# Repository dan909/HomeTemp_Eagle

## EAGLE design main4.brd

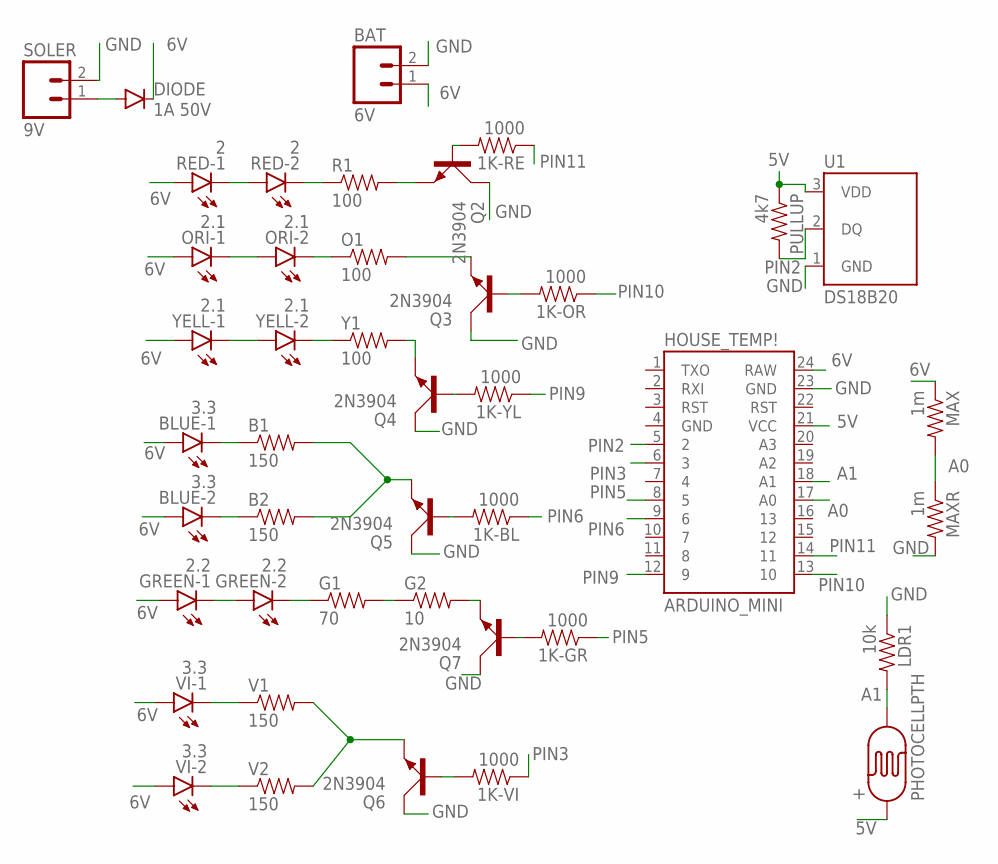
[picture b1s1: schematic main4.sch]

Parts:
1K-BL, 1K-GR, 1K-OR, 1K-RE, 1K-VI, 1K-YL: 1000; AXIAL-0.3
+: PHOTOCELLPTH; PHOTOCELL
B1, B2: 150; AXIAL-0.3
BAT: 6V; 1X02
BLUE-1, BLUE-2: 3.3; LED10MM
DIODE: 1A 50V; DIODE-1N4001
G1: 70; AXIAL-0.3
G2: 10; AXIAL-0.3
GREEN-1, GREEN-2: 2.2; LED10MM
HOUSE_TEMP!: ARDUINO_MINI
LDR1: 10k; AXIAL-0.3
MAX: 1m; AXIAL-0.3
MAXR: 1m; AXIAL-0.3
O1: 100; AXIAL-0.3
ORI-1, ORI-2: 2.1; LED10MM
PULLUP: 4k7; AXIAL-0.3
Q2, Q3, Q4, Q5, Q6, Q7: 2N3904; TO92D
R1: 100; AXIAL-0.3
RED-1, RED-2: 2; LED10MM
SOLER: 9V; 1X02
U1: DS18B20; TO-92-AMMO
V1, V2: 150; AXIAL-0.3
VI-1, VI-2: 3.3; LED10MM
Y1: 100; AXIAL-0.3
YELL-1, YELL-2: 2.1; LED10MM

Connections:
5V: +.1, HOUSE_TEMP!.21 (VCC), PULLUP.P$1 (1), U1.3 (VDD)
6V: BAT.1, BLUE-1.A, BLUE-2.A, DIODE.C, GREEN-1.A, HOUSE_TEMP!.24 (RAW), MAX.P$1 (1), ORI-1.A, RED-1.A, VI-1.A, VI-2.A, YELL-1.A
A0: HOUSE_TEMP!.17 (A0), MAX.P$2 (2), MAXR.P$1 (1)
A1: +.2, HOUSE_TEMP!.18 (A1), LDR1.P$2 (2)
BLU: B1.P$1 (1), BLUE-1.C
BLU2: B2.P$1 (1), BLUE-2.C
GND: BAT.2, HOUSE_TEMP!.23 (GND), LDR1.P$1 (1), MAXR.P$2 (2), Q2.C, Q3.C, Q4.C, Q5.C, Q6.C, Q7.C, SOLER.2, U1.1 (GND)
GREEN-2: G1.P$1 (1), GREEN-2.C
GREN: GREEN-1.C, GREEN-2.A
unnamed: R1.P$1 (1), RED-2.C
unnamed: DIODE.A, SOLER.1
unnamed: Y1.P$1 (1), YELL-2.C
unnamed: Q4.E, Y1.P$2 (2)
unnamed: B1.P$2 (2), B2.P$2 (2), Q5.E
unnamed: Q6.E, V1.P$2 (2), V2.P$2 (2)
unnamed: Q2.E, R1.P$2 (2)
unnamed: O1.P$2 (2), Q3.E
unnamed: G1.P$2 (2), G2.P$1 (1)
unnamed: G2.P$2 (2), Q7.E
unnamed: 1K-VI.P$2 (2), Q6.B
unnamed: 1K-GR.P$2 (2), Q7.B
unnamed: 1K-BL.P$2 (2), Q5.B
unnamed: 1K-YL.P$2 (2), Q4.B
unnamed: 1K-OR.P$2 (2), Q3.B
unnamed: 1K-RE.P$2 (2), Q2.B
O1: O1.P$1 (1), ORI-2.C
ORI: ORI-1.C, ORI-2.A
PIN2: HOUSE_TEMP!.5 (2), PULLUP.P$2 (2), U1.2 (DQ)
PIN3: 1K-VI.P$1 (1), HOUSE_TEMP!.6 (3)
PIN5: 1K-GR.P$1 (1), HOUSE_TEMP!.8 (5)
PIN6: 1K-BL.P$1 (1), HOUSE_TEMP!.9 (6)
PIN9: 1K-YL.P$1 (1), HOUSE_TEMP!.12 (9)
PIN10: 1K-OR.P$1 (1), HOUSE_TEMP!.13 (10)
PIN11: 1K-RE.P$1 (1), HOUSE_TEMP!.14 (11)
RED: RED-1.C, RED-2.A
VI: V1.P$1 (1), VI-1.C
VI2: V2.P$1 (1), VI-2.C
YEL: YELL-1.C, YELL-2.A

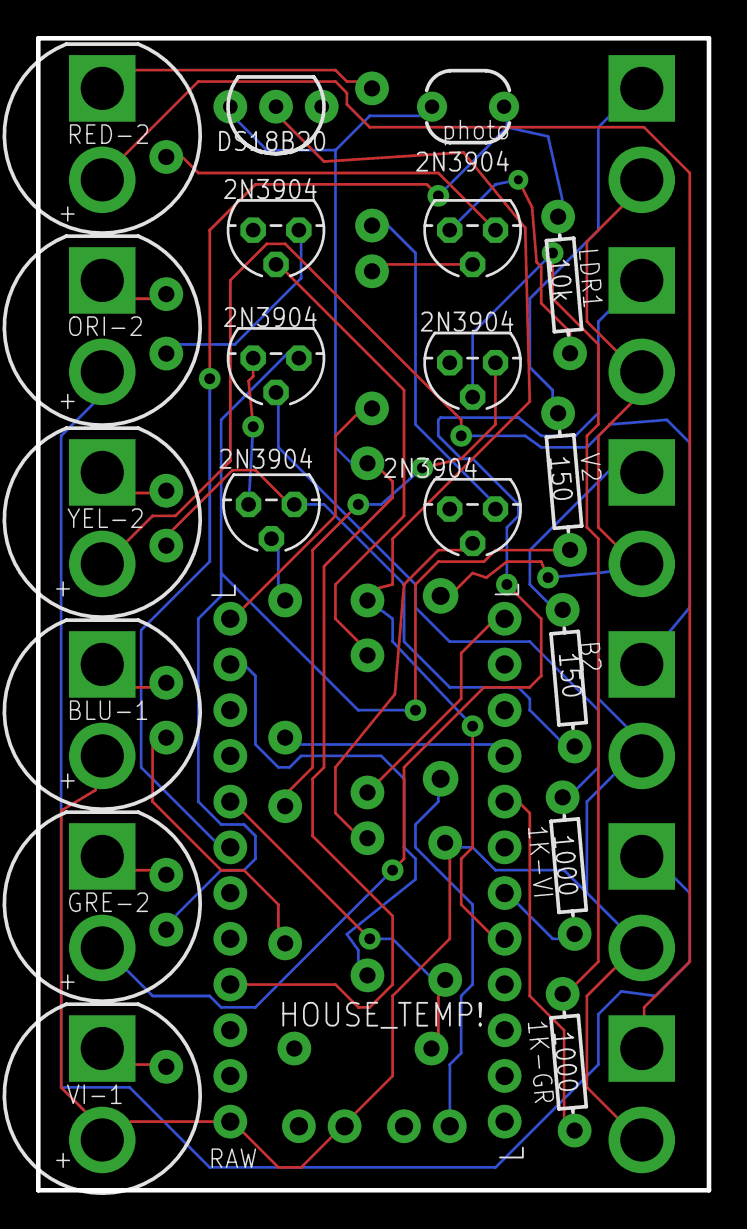
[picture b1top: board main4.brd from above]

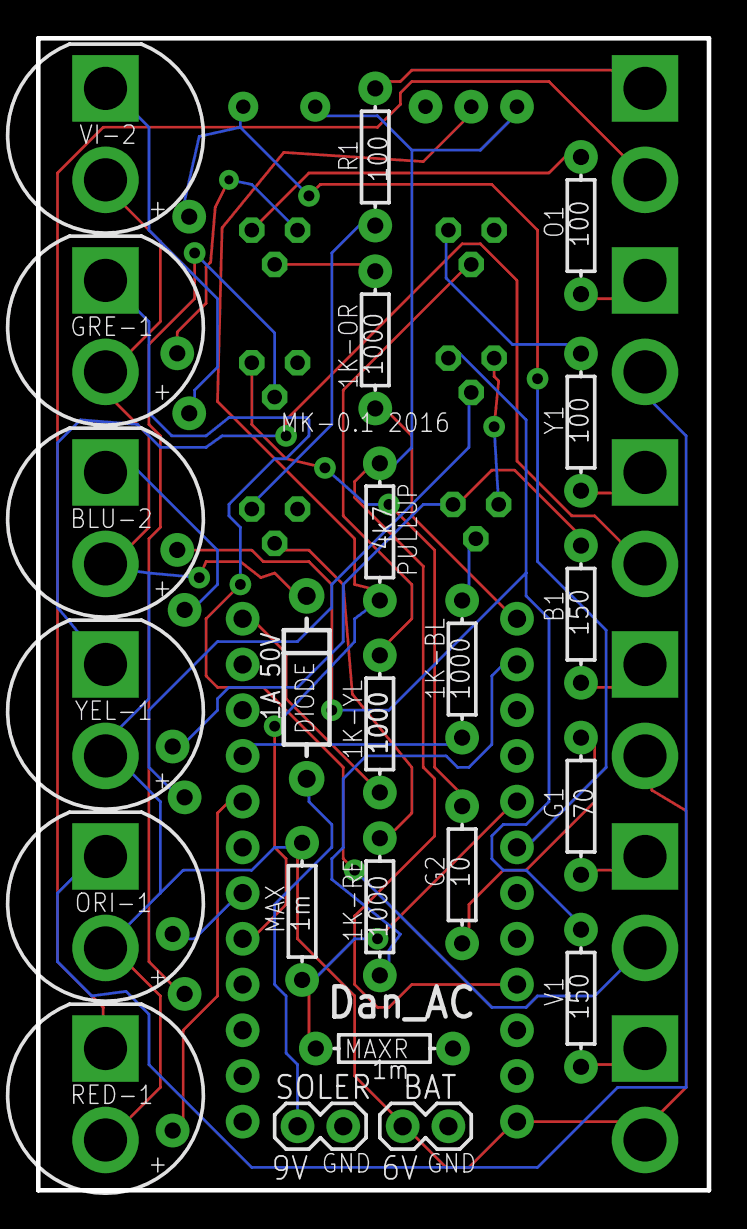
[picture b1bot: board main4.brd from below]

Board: 2 copper layers, 37.3 x 64.0 mm, 43 parts (23 on the bottom side), 38 nets.

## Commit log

2016-02-17 :octocat: Added .gitattributes & .gitignore files
2016-02-17 The Project
    A simple home temperature sensor with LEDs based on the arduino pro mini
2016-04-15 Added code file
2016-04-19 Updated night counter
2016-05-12 Added startup display
    & added stay awake for high battery voltage
2016-05-13 temp range changed
    will make dinamic based on location
2016-06-05 Better Battey manigment
2016-08-17 Improve?
    Changed min max on light display;
    made cold lights come on brightest in colder times;
    increased night threshold from 4 to 6;
    increased display part to 200 ms;
2016-09-11 line end fix
2016-10-29 A fix for sleepy temp
    changed the startup to identify low battry & added a hibenation function
    that will keep it asleep till 6.3v.

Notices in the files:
parts and their libraries:
SparkFun-LED: Licensing: Creative Commons ShareAlike 4.0 International - https://creativecommons.org/licenses/by-sa/4.0
